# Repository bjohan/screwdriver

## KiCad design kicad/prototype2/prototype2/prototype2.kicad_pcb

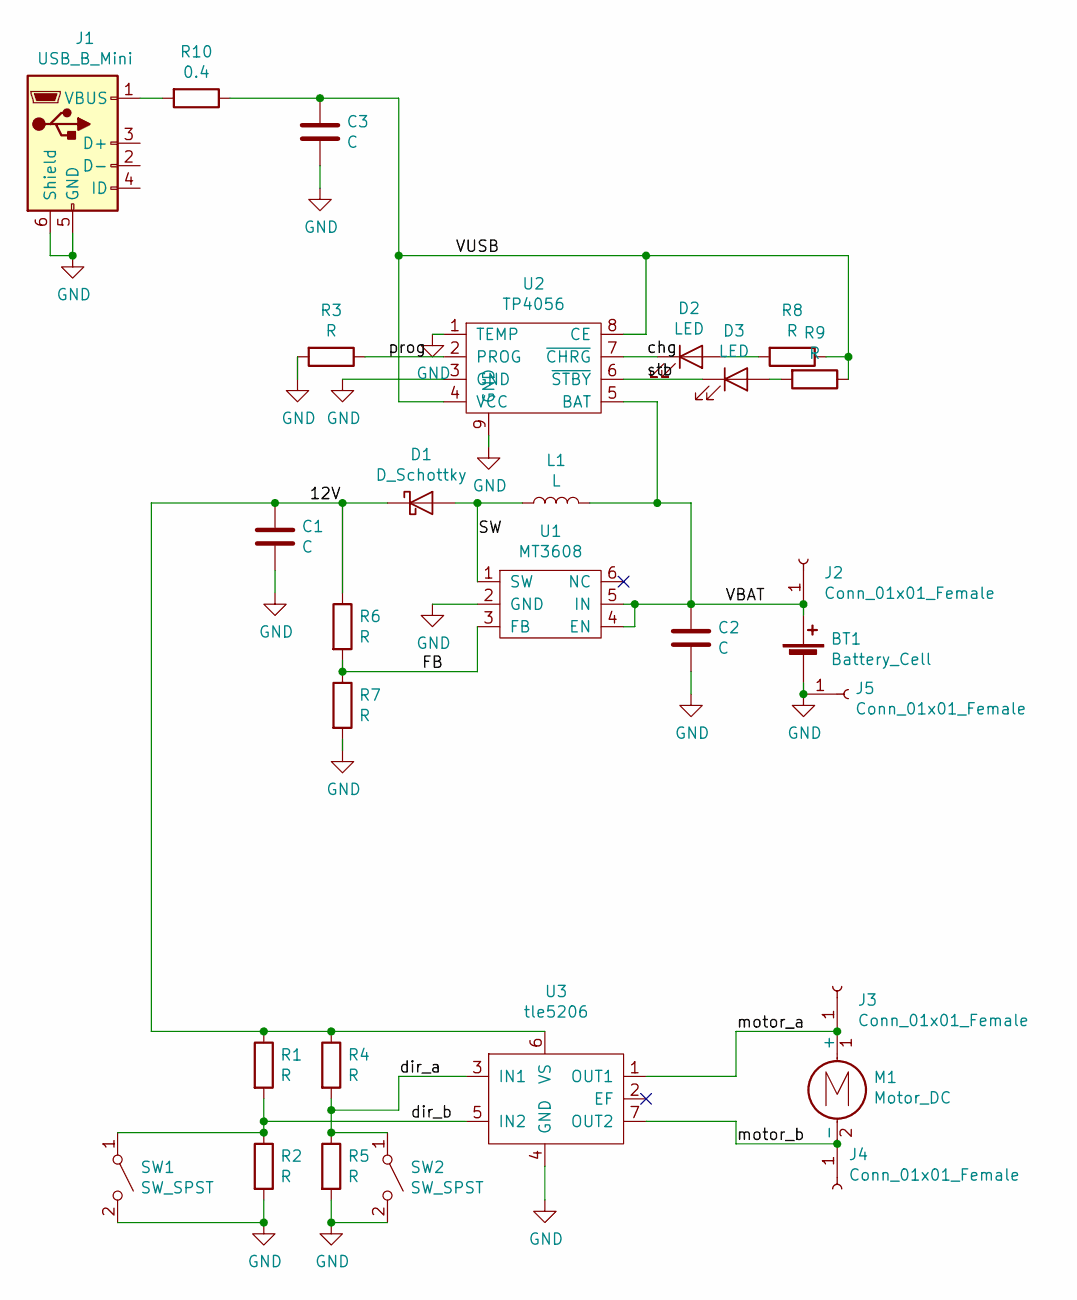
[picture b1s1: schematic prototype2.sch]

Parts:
BT1: Battery_Cell; Molex_KK-6410-02_02x2.54mm_Straight
C1, C2, C3: C; C_1206
D1: D_Schottky; D_2114
D2, D3: LED; LED_0603
J1: USB_B_Mini; USB_Mini-B
J2, J3, J4, J5: Conn_01x01_Female; PINTST
L1: L; SELF-WE-PD-XXL
M1: Motor_DC; Molex_KK-6410-02_02x2.54mm_Straight
R1, R2, R3, R4, R5, R6, R7, R8, R9: R; R_0603
R10: 0.4; R_1206
SW1, SW2: SW_SPST; SW_SPST_EVQPE1
U1: MT3608; TSOT-23-6_HandSoldering
U2: TP4056; Diodes_PSOP-8
U3: tle5206; TO-220-7_Horizontal_StaggeredType1

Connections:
/12V: C1.1, D1.1 (K), R1.1, R4.1, R6.1, U3.6 (VS)
/FB: R6.2, R7.1, U1.3 (FB)
/SW: D1.2 (A), L1.1, U1.1 (SW)
/VBAT: BT1.1 (+), C2.1, J2.1, L1.2, U1.4 (EN), U1.5 (IN), U2.5 (BAT)
/VUSB: C3.1, R8.1, R9.1, R10.1, U2.4 (VCC), U2.8 (CE)
/chg: D2.1 (K), U2.7 (~CHRG)
/dir_a: R4.2, R5.1, SW2.1 (A), U3.3 (IN1)
/dir_b: R1.2, R2.1, SW1.1 (A), U3.5 (IN2)
/motor_a: J3.1, M1.1 (+), U3.1 (OUT1)
/motor_b: J4.1, M1.2 (-), U3.7 (OUT2)
/prog: R3.1, U2.2 (PROG)
/stb: D3.1 (K), U2.6 (~STBY)
GND: BT1.2 (-), C1.2, C2.2, C3.2, J1.5 (GND), J1.6 (Shield), J5.1, R2.2, R3.2, R5.2, R7.2, SW1.2 (B), SW2.2 (B), U1.2 (GND), U2.1 (TEMP), U2.3 (GND), U2.9 (GND), U3.4 (GND)
unnamed: D2.2 (A), R8.2
unnamed: D3.2 (A), R9.2
unnamed: J1.1 (VBUS), R10.2

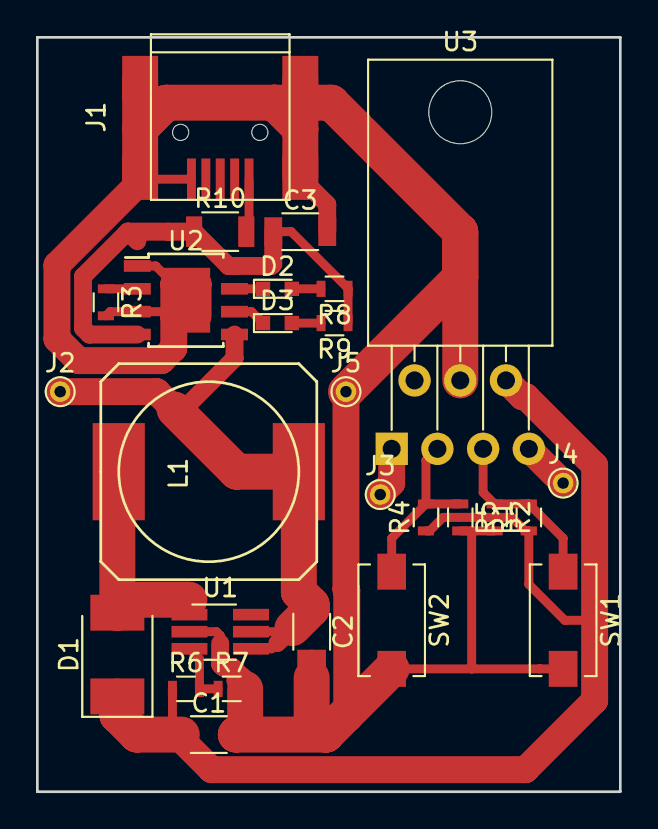
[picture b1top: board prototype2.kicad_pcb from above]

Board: 2 copper layers, 32.4 x 41.9 mm, 27 parts (0 on the bottom side), 16 nets.

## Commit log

2019-08-29 init
2019-09-03 Started prototyping
2019-09-05 more
2019-09-06 Added switch compartment
2019-09-06 Added battery and charger pcb models
2019-09-06 a little more
2019-10-12 New soap saped version
2019-10-12 electronics
2019-10-12 Started adding new electronics
